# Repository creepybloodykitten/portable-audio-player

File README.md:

# Портативный Hi-Fi аудиоплеер с локальным голосовым управлением

Портативное мультимедийное устройство, разрабатываемое с нуля: от электрической схемы и 4-слойной печатной платы до низкоуровневых драйверов Embedded Linux, инференса нейросетей на аппаратном NPU и графического интерфейса.

---

## Аппаратная платформа

* **Вычислительный модуль:** Sipeed LicheeRV Nano W (чип **Sophgo SG2002**: RISC-V 1.0 ГГц / ARM Cortex-A53, 256 МБ SIP DRAM, встроенный NPU 1 TOPS, Wi-Fi 4 / BLE 5.0).
* **Цифро-аналоговый преобразователь:** **TI PCM5102A** (32-бит / 384 кГц, аппаратный PLL, SNR 112 дБ, DirectPath без выходных разделительных конденсаторов).
* **Усилитель для наушников:** **TI TPA6132A2** (DirectPath стерео 25 мВт на канал @ 16 Ом, дифференциальный вход, подавление щелчков Pop-and-Click).
* **Аналоговая фильтрация:** Конденсаторы C0G (NP0) в звуковом тракте для исключения нелинейных искажений.
* **Дисплей:** IPS сенсорный экран с контроллером **ST7701S** (интерфейс MIPI-DSI 2 Data + 1 Clock lane, емкостный тачскрин по I2C).
* **Подсистема питания:**
  * **IP5306** — контроллер заряда 2.1 А для одного Li-Pol элемента + синхронный повышающий DC-DC конвертер 5 В 2.4 А.
  * **XC6220B331PR-G** — ультрамалошумящий LDO (3.3 В, 1 А) для изоляции аналогового питания звукового тракта от цифровых шумов и DC-DC пульсаций.
  * **TI INA219A** — прецизионный I2C-монитор тока и напряжения с шунтом для контроля АКБ (Fuel Gauge).
  * **LP803450** — Li-Pol аккумулятор (3.7 В, 1500 мА·ч) с платой защиты PCM.
* **Органы управления и разъемы:**
  * Инкрементальный энкодер **EC11** со встроенной кнопкой (регулировка громкости, Play/Pause).
  * 3 боковые тактовые кнопки с металлическими упорными кронштейнами (Power, Next Track, Voice Input).
  * 3.5 мм аудиовыход **Same Sky (CUI) SJ-3524-SMT-TR** с фиксирующими штифтами.
  * USB Type-C для зарядки и прошивки.

---

## Процесс разработки / devlog

- [x] **Этап 1. Архитектура и подбор компонентов**
  - [x] Выбор центрального компонента системы подходящий под все требования системыSoM, ЦАП, усилителя, PMIC, экрана и органов управления
  - [x] Выбор всех остальных микросхем необходимых для полноценного функционирования системы
  - [x] Повторный анализ и корректировки выбранных компонентов
- [x] **Этап 2. Схемотехника/Создание принципиальной схемы в `.kicad_sch`**
  - [x] Добавлены компоненты-модули, которые есть в основных библиотеках
  - [x] Добавлены недостающие модули(с их footprint и 3D моделью) для микросхем из специализированных сайтов (Component Search Engine)
  - [x] На основе технической документации производителей для каждой микросхемы спроектирована схема пассивной обвязки: рассчитаны и подобраны номиналы конденсаторов, резисторов и силовой индуктивности
  - [x] Сформированы все интерфейсные шины (I2S, MIPI-DSI, I2C, GPIO) и цепи питания; сформирован полный нетлист схемы без неподключенных («висящих») выводов
  - [x] Проверка Electrical Rules Check (ERC) — 0 ошибок
- [x] **Этап 3. Посадочные места и 3D-модели**
  - [x] Для всех пассивных элементов выбраны посадочные места и габариты стандартные(неоптимальные)
  - [x] Для элементов из стандартных библиотек назначены стандартные 3D модели и футпринты
  - [x] Далее была проблема с тем, чтобы найти подходящие горизонтальные кнопки, энкодер, решилась спустя немалое кол-во часов потраченных на исследование вариантов
  - [x] Для кнопок, энкодера и аккумуляторных входов были сгенерированы и проверены посадочные места и 3D модели(в случае с EC11 - 3D модель была найдена) в соответствии с их чертежами от производителей
  - [x] 100% компонентов схемы имеют назначенные футпринты
- [ ] **Этап 4. Трассировка печатной платы (PCB Layout)**
  - [x] Оптимизировал типоразмеры пассивных компонентов под плотную компоновку: уменьшил габариты корпусов, сохранив требуемые электрические характеристики и эффективность каждого компонента

---

## Документация

* [**Архитектура аппаратной части**](docs/hardware/architecture.md) — блок-схема и интерфейсы между компонентами.
* [**Аудиосистема**](docs/hardware/audio_system.md) — схема тракта ЦАП и усилителя.
* [**Подсистема питания**](docs/hardware/power_system.md) — расчеты питания, зарядки и фильтрации.
* [**Органы управления**](docs/hardware/controls.md) — схема кнопок и энкодера.

---

## Структура проекта

```text
├── docs/                   # Техническая документация аппаратной части
├── hardware/
│   └── kicad/              # Проект KiCad (схема, плата, локальные библиотеки)
│       ├── libs/           # Кастомные посадочные места и 3D-модели
│       │   ├── Custom_Battery/
│       │   ├── Custom_Buttons/
│       │   ├── EC11_Encoder/
│       │   └── SJ_3524_SMT/
│       ├── audio_player.kicad_sch
│       └── audio_player.kicad_pcb
└── software/               # Исходный код ПО, конфигурации ядра и DTS (в разработке)
```

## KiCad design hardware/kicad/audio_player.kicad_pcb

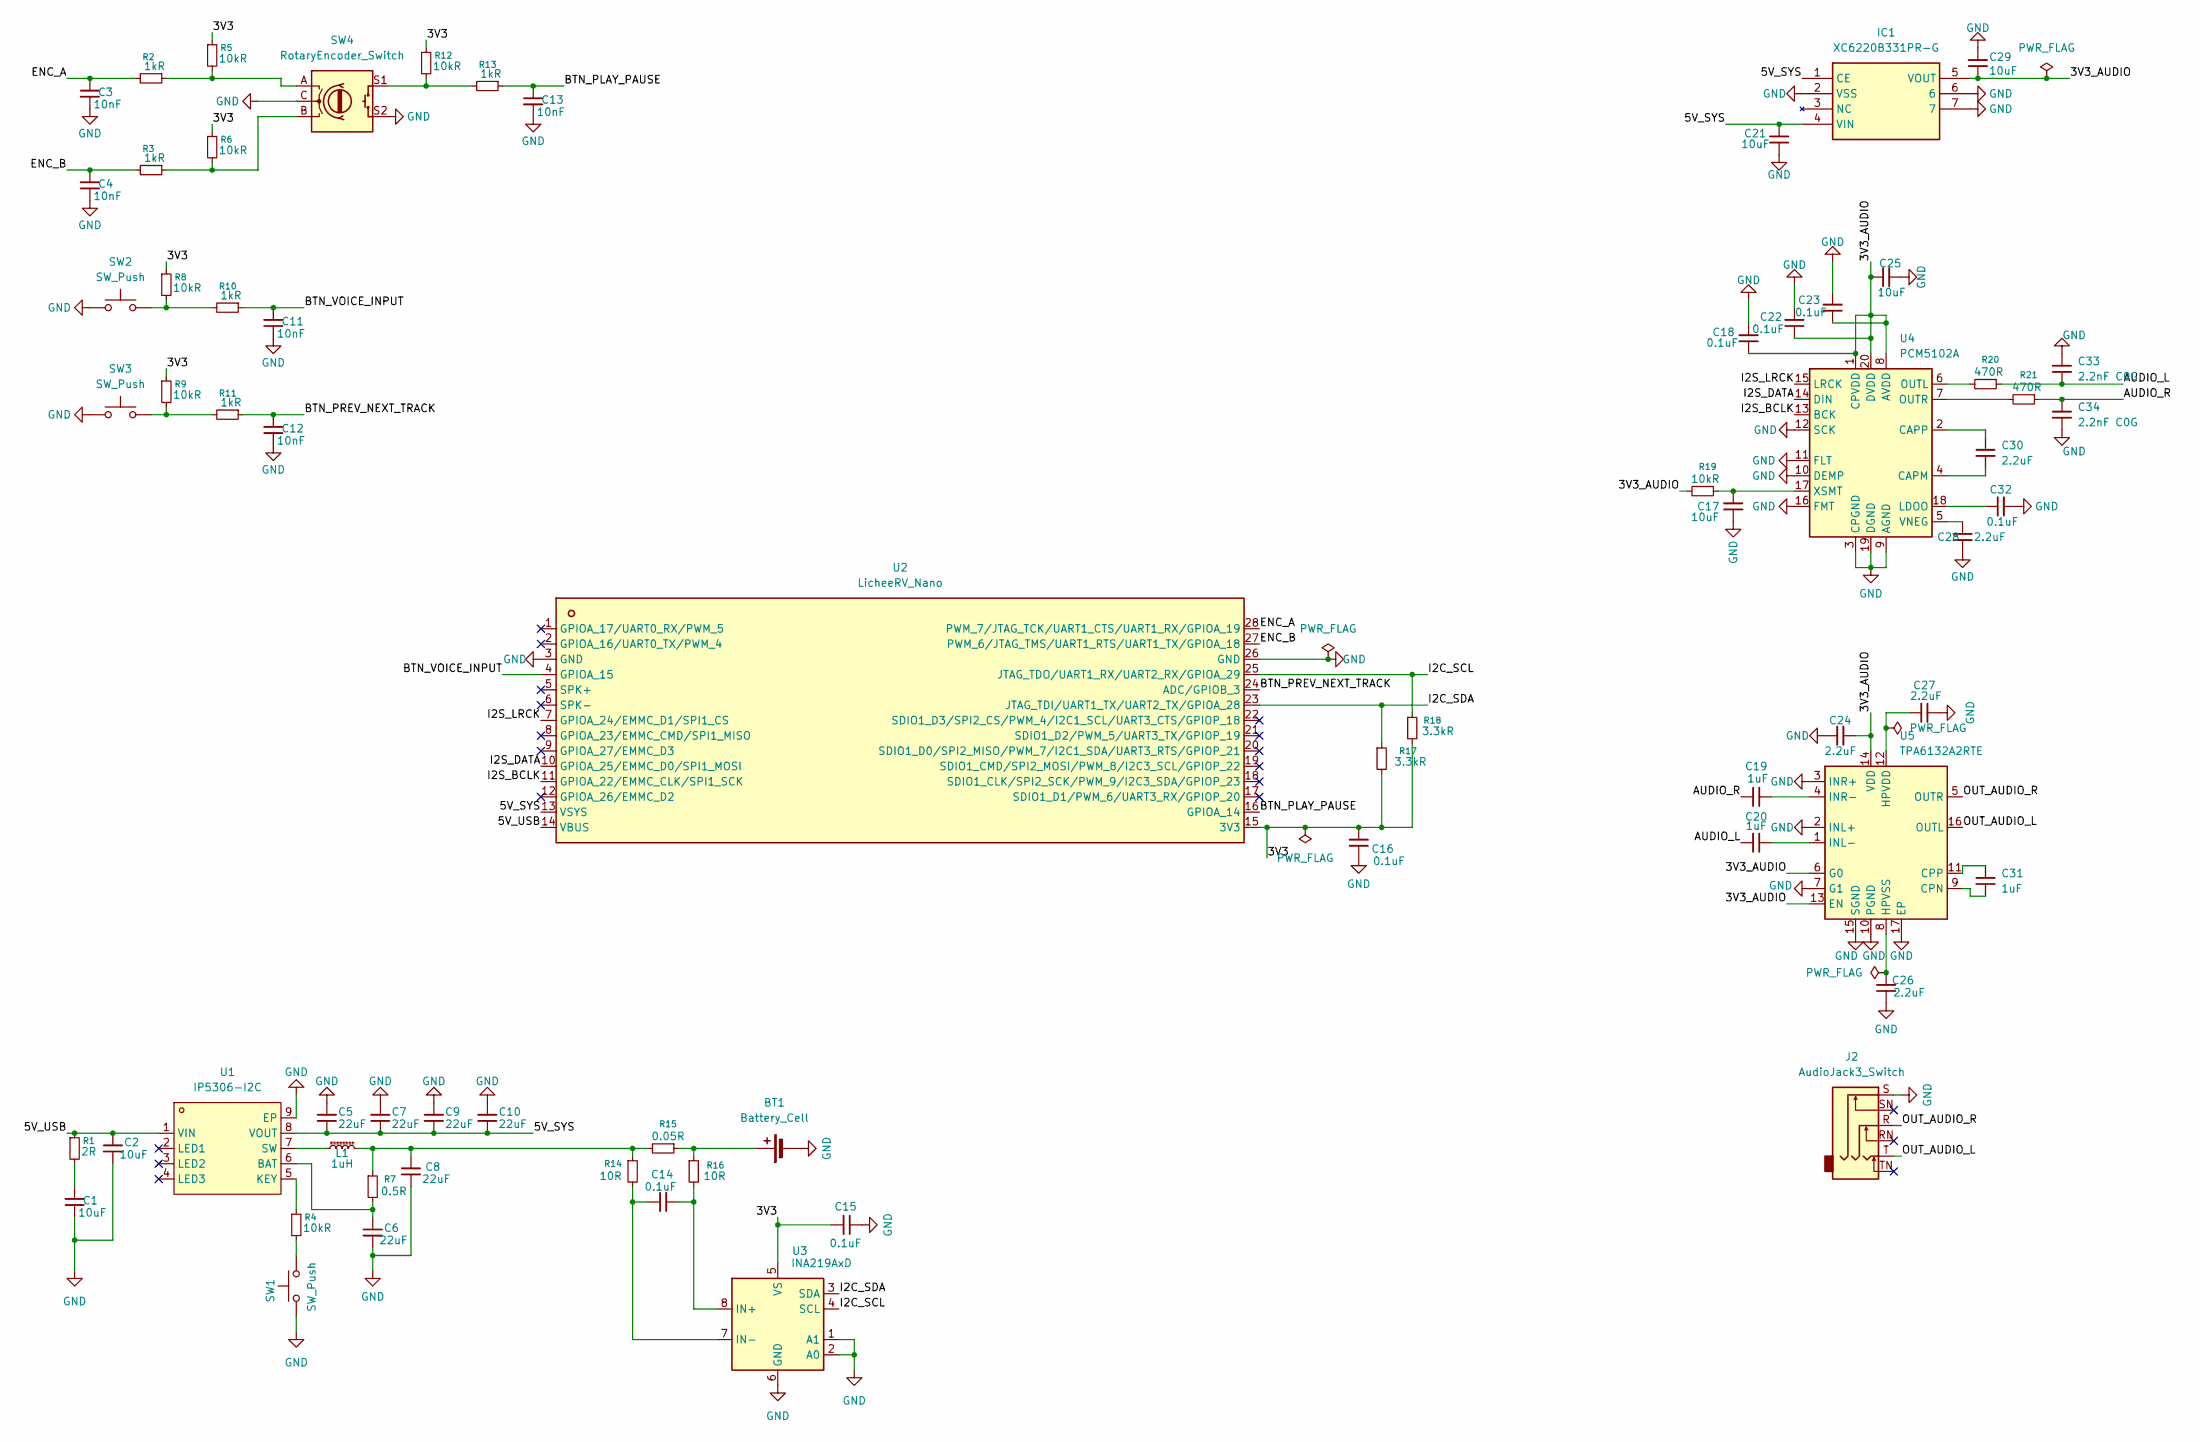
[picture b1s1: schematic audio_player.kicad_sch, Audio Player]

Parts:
BT1: Battery_Cell; Battery_Pads_2P_P4.0mm
C1, C2, C21, C25, C29: 10uF; C_0805_2012Metric
C3, C4, C11, C12, C13: 10nF; C_0402_1005Metric
C5, C6, C7, C8, C9, C10: 22uF; C_0805_2012Metric
C14, C15, C16, C18, C22, C23, C32: 0.1uF; C_0402_1005Metric
C17: 10uF; C_0603_1608Metric
C19, C20, C31: 1uF; C_0603_1608Metric
C24, C26, C27, C28, C30: 2.2uF; C_0603_1608Metric
C33, C34: 2.2nF C0G; C_0603_1608Metric
IC1: XC6220B331PR-G; XC6220B331PRG; Manufacturer_Part_Number XC6220B331PR-G; Mouser Part Number 865-XC6220B331PR-G
J2: AudioJack3_Switch; Jack_3.5mm_CUI_SJ-3524-SMT_Horizontal
L1: 1uH; L_Sunlord_SWPA4020S
R1: 2R; R_0603_1608Metric
R2, R3, R10, R11, R13: 1kR; R_0402_1005Metric
R4, R5, R6, R8, R9, R12, R19: 10kR; R_0402_1005Metric
R7: 0.5R; R_0603_1608Metric
R14, R16: 10R; R_0402_1005Metric
R15: 0.05R; R_1206_3216Metric
R17, R18: 3.3kR; R_0402_1005Metric
R20, R21: 470R; R_0402_1005Metric
SW1, SW2, SW3: SW_Push; SW_Tactile_SPST_3x6x4.3mm_Support
SW4: RotaryEncoder_Switch; RotaryEncoder_Mitsumi_SIQ-02FVS3_Horizontal
U1: IP5306-I2C; SOIC127P600X165-9N; MPN IP5306-I2C; LCSC Part C488349
U2: LicheeRV_Nano
U3: INA219AxD; SOIC-8_3.9x4.9mm_P1.27mm
U4: PCM5102A; TSSOP-20_4.4x6.5mm_P0.65mm
U5: TPA6132A2RTE; WQFN-16-1EP_3x3mm_P0.5mm_EP1.6x1.6mm_ThermalVias

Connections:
/3V3: C15.1, C16.1, R5.1, R6.1, R8.1, R9.1, R12.1, R17.2, R18.2, U2.15 (3V3), U3.5 (VS)
/3V3_AUDIO: C18.2, C22.2, C23.2, C24.2, C25.2, C29.2, IC1.5 (VOUT), R19.2, U4.1 (CPVDD), U4.8 (AVDD), U4.20 (DVDD), U5.6 (G0), U5.13 (EN), U5.14 (VDD)
/5V_SYS: C5.2, C7.2, C9.2, C10.2, C21.2, IC1.1 (CE), IC1.4 (VIN), U1.8 (VOUT), U2.13 (VSYS)
/5V_USB: C2.1, R1.1, U1.1 (VIN), U2.14 (VBUS)
/AUDIO_L: C20.1, C33.2, R20.1
/AUDIO_R: C19.1, C34.1, R21.1
/BTN_PLAY_PAUSE: C13.1, R13.1, U2.16 (GPIOA_14)
/BTN_PREV_NEXT_TRACK: C12.1, R11.1, U2.24 (ADC/GPIOB_3)
/BTN_VOICE_INPUT: C11.1, R10.1, U2.4 (GPIOA_15)
/ENC_A: C3.1, R2.2, U2.28 (PWM_7/JTAG_TCK/UART1_CTS/UART1_RX/GPIOA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)
/ENC_B: C4.1, R3.2, U2.27 (PWM_6/JTAG_TMS/UART1_RTS/UART1_TX/GPIOA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)
/I2C_SCL: R18.1, U2.25 (JTAG_TDO/UART1_RX/UART2_RX/GPIOA_29), U3.4 (SCL)
/I2C_SDA: R17.1, U2.23 (JTAG_TDI/UART1_TX/UART2_TX/GPIOA_28), U3.3 (SDA)
/I2S_BCLK: U2.11 (GPIOA_22/EMMC_CLK/SPI1_SCK), U4.13 (BCK)
/I2S_DATA: U2.10 (GPIOA_25/EMMC_D0/SPI1_MOSI), U4.14 (DIN)
/I2S_LRCK: U2.7 (GPIOA_24/EMMC_D1/SPI1_CS), U4.15 (LRCK)
/OUT_AUDIO_L: J2.T, U5.16 (OUTL)
/OUT_AUDIO_R: J2.R, U5.5 (OUTR)
GND: BT1.2 (-), C1.2, C2.2, C3.2, C4.2, C5.1, C6.2, C7.1, C8.2, C9.1, C10.1, C11.2, C12.2, C13.2, C15.2, C16.2, C17.2, C18.1, C21.1, C22.1, C23.1, C24.1, C25.1, C26.2, C27.2, C28.1, C29.1, C32.2, C33.1, C34.2, IC1.2 (VSS), IC1.6, IC1.7, J2.S, SW1.1, SW2.1, SW3.1, SW4.C, SW4.S2, U1.9 (EP), U2.3 (GND), U2.26 (GND), U3.1 (A1), U3.2 (A0), U3.6 (GND), U4.3 (CPGND), U4.9 (AGND), U4.10 (DEMP), U4.11 (FLT), U4.12 (SCK), U4.16 (FMT), U4.19 (DGND), U5.2 (INL+), U5.3 (INR+), U5.7 (G1), U5.10 (PGND), U5.15 (SGND), U5.17 (EP)
unnamed: BT1.1 (+), R15.1, R16.1
unnamed: C1.1, R1.2
unnamed: C8.1, L1.2, R7.1, R14.1, R15.2
unnamed: R2.1, R5.2, SW4.A
unnamed: R3.1, R6.2, SW4.B
unnamed: R4.2, SW1.2
unnamed: R8.2, R10.2, SW2.2
unnamed: R9.2, R11.2, SW3.2
unnamed: R12.2, R13.2, SW4.S1
unnamed: C6.1, R7.2, U1.6 (BAT)
unnamed: R4.1, U1.5 (KEY)
unnamed: L1.1, U1.7 (SW)
unnamed: C14.2, R16.2, U3.8 (IN+)
unnamed: C14.1, R14.2, U3.7 (IN-)
unnamed: C30.2, U4.4 (CAPM)
unnamed: C30.1, U4.2 (CAPP)
unnamed: C32.1, U4.18 (LDOO)
unnamed: R20.2, U4.6 (OUTL)
unnamed: R21.2, U4.7 (OUTR)
unnamed: C28.2, U4.5 (VNEG)
unnamed: C17.1, R19.1, U4.17 (XSMT)
unnamed: C31.2, U5.9 (CPN)
unnamed: C31.1, U5.11 (CPP)
unnamed: C27.1, U5.12 (HPVDD)
unnamed: C26.1, U5.8 (HPVSS)
unnamed: C20.2, U5.1 (INL-)
unnamed: C19.2, U5.4 (INR-)

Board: 4 copper layers, 68 parts (0 on the bottom side), 46 nets, no tracks yet.
